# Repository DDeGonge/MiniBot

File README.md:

# MiniBot
Super cheap super tiny bots for....well I don't know yet

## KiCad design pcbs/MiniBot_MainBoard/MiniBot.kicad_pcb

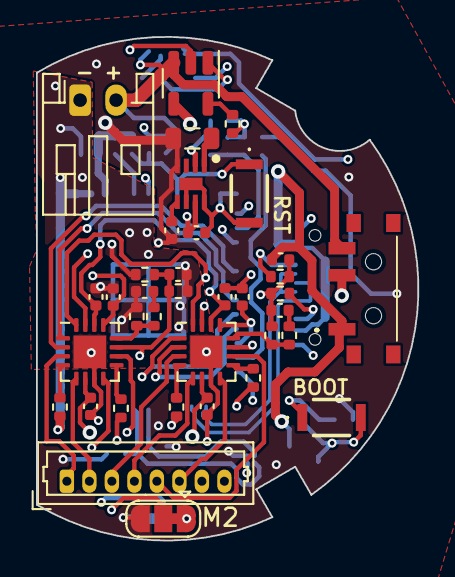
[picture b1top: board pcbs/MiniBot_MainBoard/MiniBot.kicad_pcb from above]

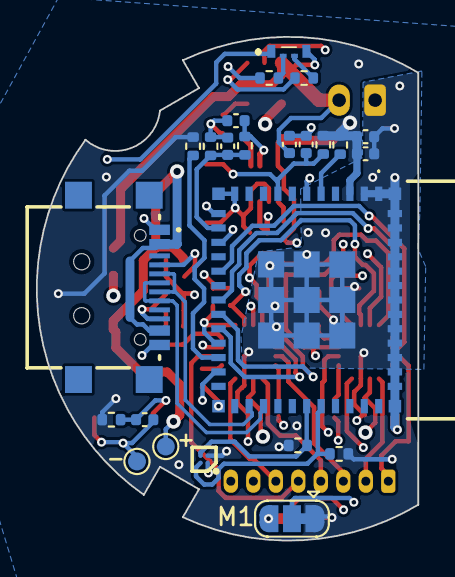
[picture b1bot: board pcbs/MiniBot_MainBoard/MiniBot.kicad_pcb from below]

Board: 4 copper layers, 21.2 x 28.0 mm, 60 parts (24 on the bottom side), 48 nets.

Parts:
C1, C8, C10: 4.7uF; C_0402_1005Metric
C2, C4, C5, C6, C9, C15, C16, C19, C20, C23: 0.1uF; C_0402_1005Metric
C3: 1uF; C_0402_1005Metric
C7: 560pF; C_0402_1005Metric
C17, C21: 10uF; C_0402_1005Metric
C18, C22: 22nF; C_0402_1005Metric
IC1: MMC5633NJL; BGA4C40P2X2_85X85X60
IC2: MIC23050-SYML-TR; SON50P200X200X90-9N-D
J1: Conn_01x08; Molex_PicoBlade_53047-0810_1x08_P1.25mm_Vertical
J2: Conn_01x02; JST_PH_S2B-PH-K_1x02_P2.00mm_Horizontal
J3: GSB1C41110SSHR
JP1, JP2: Jumper_3_Bridged12; SolderJumper-3_P1.3mm_Bridged12_RoundedPad1.0x1.5mm
L1: L; L_0805_2012Metric
LED1: EASV2010RWA0
R1, R2, R14, R15: 5.1k; R_0402_1005Metric
R3, R4, R5, R6, R9, R12: 10k; R_0402_1005Metric
R7, R10, R11: 390k; R_0402_1005Metric
R8: 12.4k; R_0402_1005Metric
R13, R16, R20: 1k; R_0402_1005Metric
R18, R19, R22, R23: 1; R_0402_1005Metric
R24, R25: 47k; R_0402_1005Metric
S1: PCM12SMTR
S2, S3: EVP-AWBD4A; EVPAWBD4A
TP1, TP2: TestPoint; TestPoint_Pad_D1.0mm
U1: ESP32-C3-MINI-1-H4X; ESP32C3MINI1H4X
U3: MCP73832-2-OT; SOT-23-5
U4, U5: STSPIN220; VQFN-16-1EP_3x3mm_P0.5mm_EP1.8x1.8mm

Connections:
+3V3: C1.2, C2.1, C7.1, IC1.B1 (VDD), IC2.4 (SNS), JP1.3 (B), JP2.1 (A), L1.1, R1.1, R2.1, R3.1, R5.1, R6.1, R7.1, R9.1, U1.3 (3V3)
+5V: C9.1, J3.A4 (VBUS_1), J3.A9 (VBUS_2), S1.1 (NC), TP2.1, U3.4 (V_{DD})
+BATT: C10.1, J2.2, LED1.4 (R6+), S1.3 (NO), U3.3 (V_{BAT})
/CC1: J3.A5 (CC1), R14.1
/CC2: J3.B5 (CC2), R15.1
/CFF: C7.2, IC2.5 (CFF)
/GPIO2: R6.2, U1.5 (IO2)
/GPIO8: R5.2, U1.22 (IO8)
/GPIO9: C5.1, R9.2, S3.A1 (NO), U1.23 (IO9)
/LED_R: LED1.3 (R6-), R13.1
/LED_W: LED1.1 (T1+), U1.12 (IO0)
/M0_A1: J1.1, U4.3 (OUTA1)
/M0_A2: J1.2, U4.5 (OUTA2)
/M0_B1: J1.8, U4.10 (OUTB1)
/M0_B2: J1.7, U4.8 (OUTB2)
/M0_DIR: U1.18 (IO4), U4.1 (DIR)
/M0_STEP: U1.16 (IO10), U4.2 (STCK)
/M1_A1: J1.3, U5.3 (OUTA1)
/M1_A2: J1.4, U5.5 (OUTA2)
/M1_B1: J1.5, U5.10 (OUTB1)
/M1_B2: J1.6, U5.8 (OUTB2)
/M1_DIR: U1.19 (IO5), U5.1 (DIR)
/M1_STEP: U1.20 (IO6), U5.2 (STCK)
/MODE1: JP2.2 (C), U4.16 (MODE1), U5.16 (MODE1)
/MODE2: JP1.2 (C), U4.15 (MODE2), U5.15 (MODE2)
/M_EN: C15.1, C19.1, U1.21 (IO7), U4.13 (EN/FLT), U5.13 (EN/FLT)
/M_RST: C16.1, C20.1, U1.6 (IO3), U4.14 (STBY/RESET), U5.14 (STBY/RESET)
/RST: C3.1, R3.2, S2.A1 (NO), U1.8 (EN)
/SCL: IC1.A2 (SCL), R1.2, U1.31 (TXD0)
/SDA: IC1.B2 (SDA), R2.2, U1.30 (RXD0)
/USB+: J3.A6 (DP1), J3.B6 (DP2), U1.27 (IO19)
/USB-: J3.A7 (DN1), J3.B7 (DN2), U1.26 (IO18)
/VREF: C4.1, R7.2, R8.1, U4.11 (REF), U5.11 (REF)
/VSENSE: C6.1, R10.2, R11.1, U1.13 (IO1)
GND: C1.1, C2.2, C3.2, C4.2, C5.2, C6.2, C8.2, C9.2, C10.2, C15.2, C16.2, C17.2, C18.2, C19.2, C20.2, C21.2, C22.2, C23.2, IC1.A1 (VSA), IC2.6 (AGND), IC2.8 (PGND), IC2.9 (EP), J2.1, J3.A1 (GND_1), J3.A12 (GND_2), JP1.1 (A), JP2.3 (B), R4.2, R8.2, R11.2, R12.2, R14.2, R15.2, R18.2, R19.2, R22.2, R23.2, R24.2, R25.2, S2.A2 (COM), S3.A2 (COM), TP1.1, U1.1 (GND_1), U1.2 (GND_2), U1.11 (GND_3), U1.14 (GND_4), U1.36 (GND_5), U1.37 (GND_6), U1.38 (GND_7), U1.39 (GND_8), U1.40 (GND_9), U1.41 (GND_10), U1.42 (GND_11), U1.43 (GND_12), U1.44 (GND_13), U1.45 (GND_14), U1.46 (GND_15), U1.47 (GND_16), U1.48 (GND_17), U1.49 (GND_18), U1.50 (GND_19), U1.51 (GND_20), U1.52 (GND_21), U1.53 (GND_22), U1.54 (GND_23), U1.55 (GND_24), U1.56 (GND_25), U1.57 (GND_26), U1.58 (GND_27), U1.59 (GND_28), U1.60 (GND_29), U1.61 (GND_30), U3.2 (V_{SS}), U4.7 (GND), U4.17 (EPAD), U5.7 (GND), U5.17 (EPAD)
unnamed: C18.1, R16.2
unnamed: C22.1, R20.2
unnamed: IC2.1 (SW), L1.2
unnamed: LED1.2 (T1-), R4.1
unnamed: R12.1, U3.5 (PROG)
unnamed: R13.2, U3.1 (STAT)
unnamed: R19.1, U4.4 (SENSEA)
unnamed: R18.1, U4.9 (SENSEB)
unnamed: R16.1, R24.1, U4.12 (TOFF)
unnamed: R23.1, U5.4 (SENSEA)
unnamed: R22.1, U5.9 (SENSEB)
unnamed: R20.1, R25.1, U5.12 (TOFF)
VDC: C8.1, C17.1, C21.1, C23.1, IC2.2 (EN), IC2.7 (VIN), R10.1, S1.2 (COM), U4.6 (VS), U5.6 (VS)

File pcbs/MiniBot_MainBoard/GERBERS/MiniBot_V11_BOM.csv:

Item #,*Designator,*Qty,Manufacturer,*Mfg Part #,Description / Value,*Package/Footprint,Type,Your Instructions / Notes
1,U1,1,Espressif Systems,ESP32-C3-MINI-1-H4X,ESP32-C3-MINI-1-H4X,ESP32C3MINI1H4X,SMD,
2,U3,1,Microchip Technology,MCP73832-2-OT,IC BATT CONTRL LI-ION 1CELL 8DFN,8-VFDFN,SMD,
3,"U4,U5",2,STMicroelectronics,STSPIN220,LOW VOLTAGE STEPPER MOTOR DRIVER,VQFN-16,SMD,
4,IC1,1,Memsic Inc.,MMC5633NJL,SEN MR I2C/I3C 4-WLP,4-WLP,BGA,
5,IC2,1,Microchip Technology,MIC23050-SYML-TR,High Efficiency 600mA Buck Switcher,8-VFDFN,SMD,
6,S1,1,C&K,PCM12SMTR,SWITCH SLIDE SPDT 300MA 6V,SMD,SMD,
7,"S2,S3",2,Panasonic,EVP-AWBD4A,Tactile Switches EVP-AWBD4A,SMD,SMD,
8,L1,1,TKD,MLZ2012N1R0LT000,Power Inductors - SMD 1 UH 20%,805,SMD,
9,LED1,1,Everlight Electronics Co Ltd,EASV2010RWA0,LED RED/WHITE DIFFUSED 4SMD R/A,SMD,SMD,
10,"R22,R19,R23,R18",4,YAGEO,RC0402FR-7W1RL,RES 1 OHM 1% 1/8W 0402,402,SMD,Substitutions OK
11,"R20,R16,R13",3,YAGEO,RC0402FR-071KL,RES 1K OHM 1% 1/16W 0402,402,SMD,Substitutions OK
12,"R15,R14,R1,R2",4,YAGEO,RC0402FR-135K1L,RES 5.1K OHM 1% 1/16W 0402,402,SMD,Substitutions OK
13,"R12,R9,R3,R5,R4,R6",6,YAGEO,RC0402FR-0710KL,RES 10K OHM 1% 1/16W 0402,402,SMD,Substitutions OK
14,R8,1,YAGEO,RC0402FR-0712K4L,RES 12.4K OHM 1% 1/16W 0402,402,SMD,Substitutions OK
15,"R24,R25",2,YAGEO,RC0402FR-0747KL,RES 47K OHM 1% 1/16W 0402,402,SMD,Substitutions OK
16,"R7,R10,R11",3,YAGEO,RC0402FR-07390KL,RES 390K OHM 1% 1/16W 0402,402,SMD,Substitutions OK
17,C7,1,Murata Electronics,GRM1555C1H561JA01D,CAP CER 560PF 50V C0G/NP0 0402,402,SMD,Substitutions OK
18,"C22,C18",2,Murata Electronics,GRM155R71C223KA01D,CAP CER 0.022UF 16V X7R 0402,402,SMD,Substitutions OK
19,"C16,C9,C19,C15,C20,C23,C4,C5,C6,C2",10,Murata Electronics,GRM155R71C104KA88J,CAP CER 0.1 uF 16 VDC 10% 0402 X7R,402,SMD,Substitutions OK
20,C3,1,Murata Electronics,GCM155C71A105KE38D,CAP CER 1UF 10V X7S 0402,402,SMD,Substitutions OK
21,"C1,C10,C8",3,Murata Electronics,GRM155R60J475ME47D,CAP CER 4.7UF 6.3V X5R 0402,402,SMD,Substitutions OK
22,"C21,C17",2,Murata Electronics,GRM155R60J106ME05J,CAP CER 10UF 6.3V X5R 0402,402,SMD,Substitutions OK
23,J1,1,Molex,530470810,CONN HEADER VERT 8POS 1.25MM,1x08_P1.25mm,Through Hole,
24,J2,1,JST,S2B-PH-K-S,CONN HEADER R/A 2POS 2MM,1x02_P2.00mm,Through Hole,
25,J3,1,Amphenol Canada,GSB1C41110SSHR,USB Connectors USB2.0 TYPE C,SMD,SMD,

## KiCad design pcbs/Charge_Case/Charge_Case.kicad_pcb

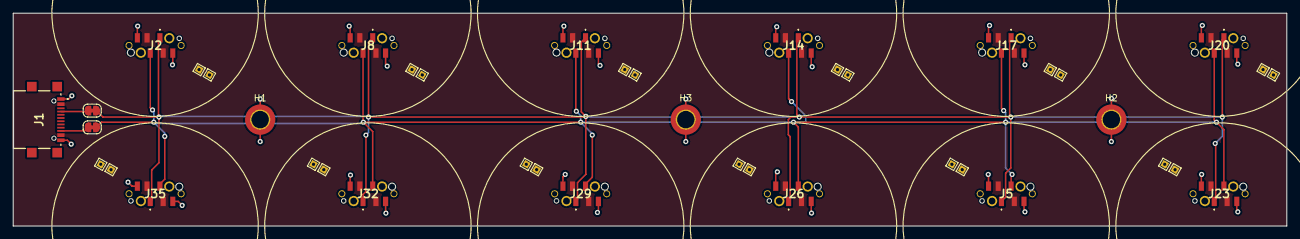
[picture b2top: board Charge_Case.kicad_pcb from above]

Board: 2 copper layers, 197.5 x 33.0 mm, 42 parts (0 on the bottom side), 8 nets.

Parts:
H1, H2, H3: MountingHole_Pad; MountingHole_2.7mm_M2.5_DIN965_Pad_TopOnly
J1: GSB1C41110SSHR
J2, J5, J8, J11, J14, J17, J20, J23, J26, J29, J32, J35: USB4180-03-0120-C; USB4180030120C
J3, J4, J6, J7, J9, J10, J12, J13, J15, J16, J18, J19, J21, J22, J24, J25, J27, J28, J30, J31, J33, J34, J36, J37: Conn_01x01; TestPoint_THTPad_1.0x1.0mm_Drill0.5mm
JP1, JP2: Jumper_2_Bridged; SolderJumper-2_P1.3mm_Bridged_RoundedPad1.0x1.5mm

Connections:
+5V: J1.A4 (VBUS_1), J1.A9 (VBUS_2), J2.A9 (VBUS_1), J2.B9 (VBUS_2), J3.1, J5.A9 (VBUS_1), J5.B9 (VBUS_2), J6.1, J8.A9 (VBUS_1), J8.B9 (VBUS_2), J9.1, J11.A9 (VBUS_1), J11.B9 (VBUS_2), J12.1, J14.A9 (VBUS_1), J14.B9 (VBUS_2), J15.1, J17.A9 (VBUS_1), J17.B9 (VBUS_2), J18.1, J20.A9 (VBUS_1), J20.B9 (VBUS_2), J21.1, J23.A9 (VBUS_1), J23.B9 (VBUS_2), J24.1, J26.A9 (VBUS_1), J26.B9 (VBUS_2), J27.1, J29.A9 (VBUS_1), J29.B9 (VBUS_2), J30.1, J32.A9 (VBUS_1), J32.B9 (VBUS_2), J33.1, J35.A9 (VBUS_1), J35.B9 (VBUS_2), J36.1
/CC1: J2.A5 (CC1), J5.A5 (CC1), J8.A5 (CC1), J11.A5 (CC1), J14.A5 (CC1), J17.A5 (CC1), J20.A5 (CC1), J23.A5 (CC1), J26.A5 (CC1), J29.A5 (CC1), J32.A5 (CC1), J35.A5 (CC1), JP1.1 (A)
/CC1_SRC: J1.A5 (CC1), JP1.2 (B)
/CC2: J2.B5 (CC2), J5.B5 (CC2), J8.B5 (CC2), J11.B5 (CC2), J14.B5 (CC2), J17.B5 (CC2), J20.B5 (CC2), J23.B5 (CC2), J26.B5 (CC2), J29.B5 (CC2), J32.B5 (CC2), J35.B5 (CC2), JP2.1 (A)
/CC2_SRC: J1.B5 (CC2), JP2.2 (B)
GND: H1.1, H2.1, H3.1, J1.A1 (GND_1), J1.A12 (GND_2), J2.A12 (GND_1), J2.B12 (GND_2), J4.1, J5.A12 (GND_1), J5.B12 (GND_2), J7.1, J8.A12 (GND_1), J8.B12 (GND_2), J10.1, J11.A12 (GND_1), J11.B12 (GND_2), J13.1, J14.A12 (GND_1), J14.B12 (GND_2), J16.1, J17.A12 (GND_1), J17.B12 (GND_2), J19.1, J20.A12 (GND_1), J20.B12 (GND_2), J22.1, J23.A12 (GND_1), J23.B12 (GND_2), J25.1, J26.A12 (GND_1), J26.B12 (GND_2), J28.1, J29.A12 (GND_1), J29.B12 (GND_2), J31.1, J32.A12 (GND_1), J32.B12 (GND_2), J34.1, J35.A12 (GND_1), J35.B12 (GND_2), J37.1
unnamed: J1.A6 (DP1), J1.A7 (DN1)
unnamed: J1.B6 (DP2), J1.B7 (DN2)

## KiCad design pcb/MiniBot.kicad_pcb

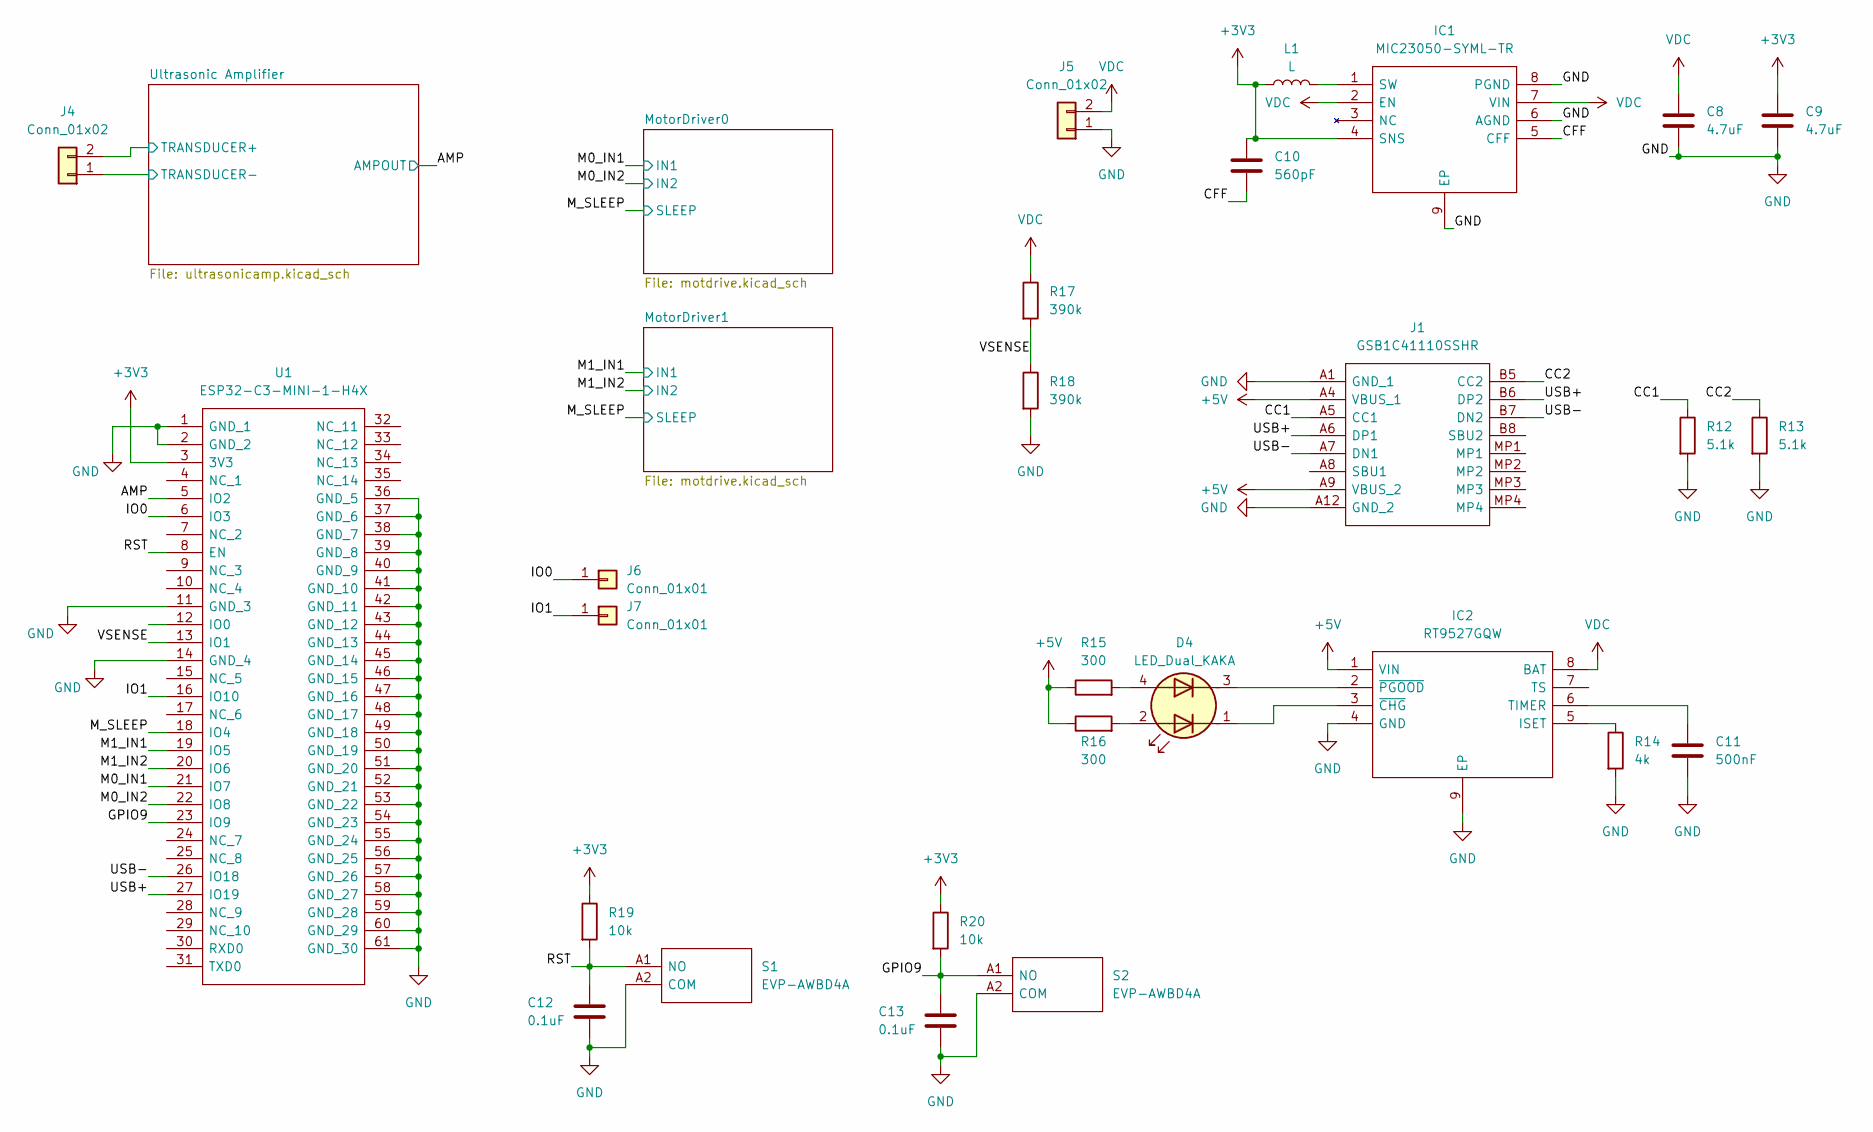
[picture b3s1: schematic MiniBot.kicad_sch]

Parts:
C8, C9: 4.7uF; C_0402_1005Metric
C10: 560pF; C_0402_1005Metric
C11: 500nF; C_0402_1005Metric
C12, C13: 0.1uF; C_0402_1005Metric
D4: LED_Dual_KAKA; SB0603WC01-RG
IC1: MIC23050-SYML-TR; SON50P200X200X90-9N-D; Mouser Part Number 998-MIC23050-SYMLTR
IC2: RT9527GQW; SON50P200X200X80-9N; Mouser Part Number 835-RT9527GQW
J1: GSB1C41110SSHR; Manufacturer_Part_Number GSB1C41110SSHR
J4: Conn_01x02; Transducer
J5: Conn_01x02; JST_PH_S2B-PH-K_1x02_P2.00mm_Horizontal
J6, J7: Conn_01x01; TestPoint_Pad_D1.0mm
L1: L; L_0805_2012Metric
R12, R13: 5.1k; R_0402_1005Metric
R14: 4k; R_0402_1005Metric
R15, R16: 300; R_0402_1005Metric
R17, R18: 390k; R_0402_1005Metric
R19, R20: 10k; R_0402_1005Metric
S1, S2: EVP-AWBD4A; EVPAWBD4A; Mouser Part Number 667-EVP-AWBD4A
U1: ESP32-C3-MINI-1-H4X; ESP32C3MINI1H4X; Mouser Part Number 356-ESP32C3MINI1H4X

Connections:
+3V3: C9.1, C10.1, IC1.4 (SNS), L1.1, R19.1, R20.1, U1.3 (3V3); also elsewhere on the board
+5V: IC2.1 (VIN), J1.A4 (VBUS_1), J1.A9 (VBUS_2), R15.1, R16.1
/AMP: U1.5 (IO2); also elsewhere on the board
/CC1: J1.A5 (CC1), R12.1
/CC2: J1.B5 (CC2), R13.1
/CFF: C10.2, IC1.5 (CFF)
/GPIO9: C13.1, R20.2, S2.A1 (NO), U1.23 (IO9)
/IO0: J6.1, U1.6 (IO3)
/IO1: J7.1, U1.16 (IO10)
/M0_IN1: U1.21 (IO7); also elsewhere on the board
/M0_IN2: U1.22 (IO8); also elsewhere on the board
/M1_IN1: U1.19 (IO5); also elsewhere on the board
/M1_IN2: U1.20 (IO6); also elsewhere on the board
/M_SLEEP: U1.18 (IO4); also elsewhere on the board
/RST: C12.1, R19.2, S1.A1 (NO), U1.8 (EN)
/USB+: J1.A6 (DP1), J1.B6 (DP2), U1.27 (IO19)
/USB-: J1.A7 (DN1), J1.B7 (DN2), U1.26 (IO18)
/Ultrasonic Amplifier/IN1+: J4.2; also elsewhere on the board
/VSENSE: R17.2, R18.1, U1.13 (IO1)
GND: C8.2, C9.2, C11.2, C12.2, C13.2, IC1.6 (AGND), IC1.8 (PGND), IC1.9 (EP), IC2.4 (GND), IC2.9 (EP), J1.A1 (GND_1), J1.A12 (GND_2), J4.1, J5.1, R12.2, R13.2, R14.2, R18.2, S1.A2 (COM), S2.A2 (COM), U1.1 (GND_1), U1.2 (GND_2), U1.11 (GND_3), U1.14 (GND_4), U1.36 (GND_5), U1.37 (GND_6), U1.38 (GND_7), U1.39 (GND_8), U1.40 (GND_9), U1.41 (GND_10), U1.42 (GND_11), U1.43 (GND_12), U1.44 (GND_13), U1.45 (GND_14), U1.46 (GND_15), U1.47 (GND_16), U1.48 (GND_17), U1.49 (GND_18), U1.50 (GND_19), U1.51 (GND_20), U1.52 (GND_21), U1.53 (GND_22), U1.54 (GND_23), U1.55 (GND_24), U1.56 (GND_25), U1.57 (GND_26), U1.58 (GND_27), U1.59 (GND_28), U1.60 (GND_29), U1.61 (GND_30); also elsewhere on the board
unnamed: D4.1 (A1), IC2.3 (~CHG)
unnamed: D4.3 (A2), IC2.2 (~PGOOD)
unnamed: D4.2 (K1), R16.2
unnamed: D4.4 (K2), R15.2
unnamed: IC1.1 (SW), L1.2
unnamed: IC2.5 (ISET), R14.1
unnamed: C11.1, IC2.6 (TIMER)
VDC: C8.1, IC1.2 (EN), IC1.7 (VIN), IC2.8 (BAT), J5.2, R17.1; also elsewhere on the board

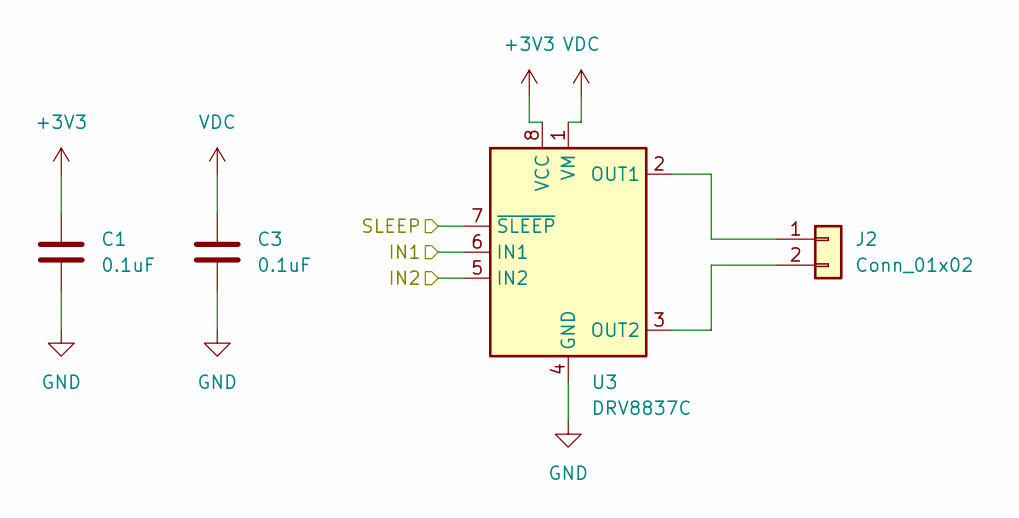
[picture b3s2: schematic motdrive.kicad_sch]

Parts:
C1, C3: 0.1uF; C_0402_1005Metric
J2: Conn_01x02; PinHeader_1x02_P1.27mm_Vertical
U3: DRV8837C; WSON-8-1EP_2x2mm_P0.5mm_EP0.9x1.6mm

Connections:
+3V3: C1.1, U3.8 (VCC); also elsewhere on the board
/M0_IN1: U3.6 (IN1); also elsewhere on the board
/M0_IN2: U3.5 (IN2); also elsewhere on the board
/M_SLEEP: U3.7 (~SLEEP); also elsewhere on the board
GND: C1.2, C3.2, U3.4 (GND), U3.9 (GND); also elsewhere on the board
unnamed: J2.1, U3.2 (OUT1)
unnamed: J2.2, U3.3 (OUT2)
VDC: C3.1, U3.1 (VM); also elsewhere on the board

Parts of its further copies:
C2, C4: 0.1uF; C_0402_1005Metric
J3: Conn_01x02; PinHeader_1x02_P1.27mm_Vertical
U4: DRV8837C; WSON-8-1EP_2x2mm_P0.5mm_EP0.9x1.6mm

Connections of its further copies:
+3V3: C2.1, U4.8 (VCC); also elsewhere on the board
/M1_IN1: U4.6 (IN1); also elsewhere on the board
/M1_IN2: U4.5 (IN2); also elsewhere on the board
/M_SLEEP: U4.7 (~SLEEP); also elsewhere on the board
GND: C2.2, C4.2, U4.4 (GND), U4.9 (GND); also elsewhere on the board
unnamed: J3.1, U4.2 (OUT1)
unnamed: J3.2, U4.3 (OUT2)
VDC: C4.1, U4.1 (VM); also elsewhere on the board

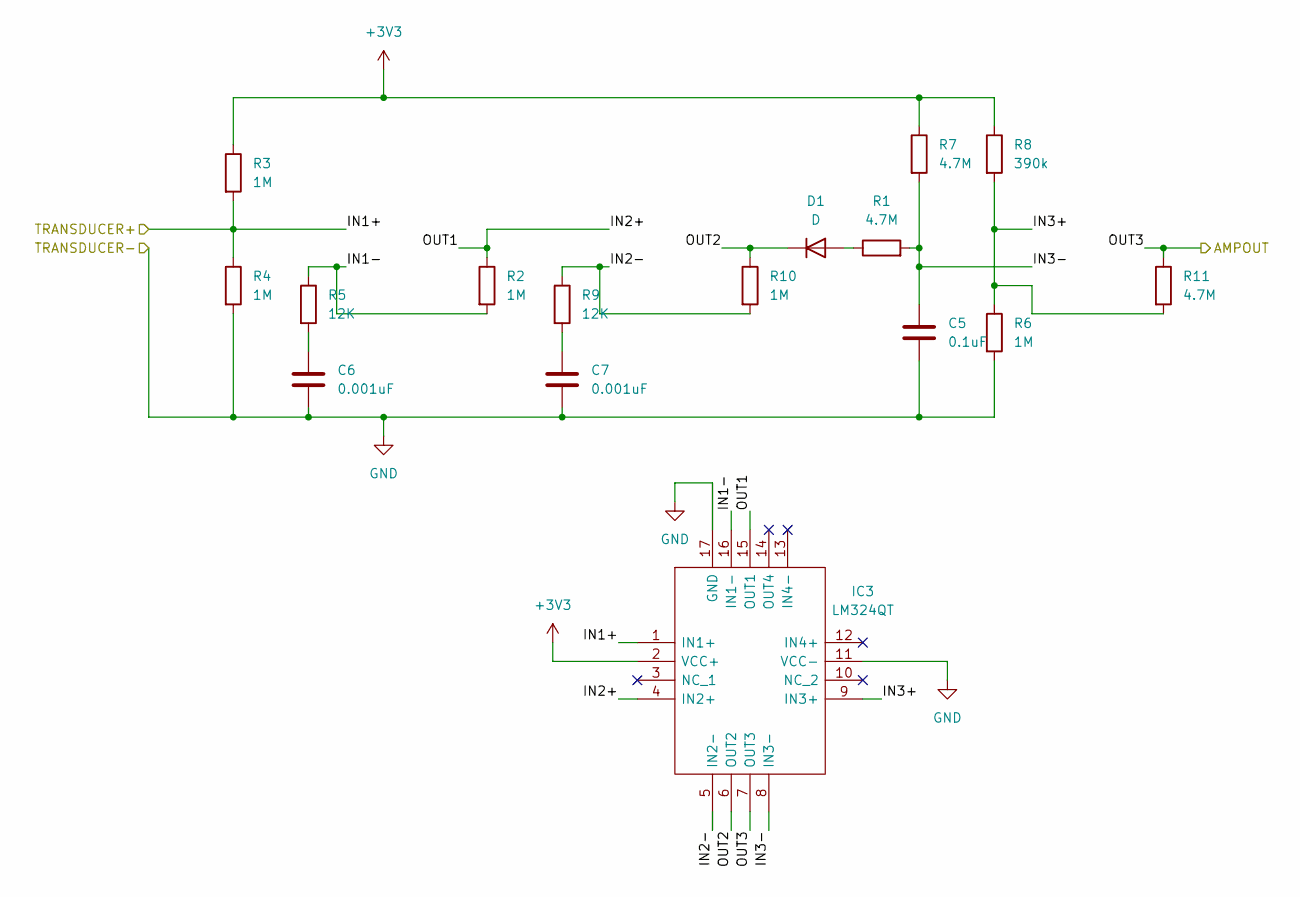
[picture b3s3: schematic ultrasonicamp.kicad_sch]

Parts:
C5: 0.1uF; C_0402_1005Metric
C6, C7: 0.001uF; C_0402_1005Metric
D1: D; D_0402_1005Metric
IC3: LM324QT; QFN50P300X300X100-17N; Mouser Part Number 511-LM324QT
R1, R7, R11: 4.7M; R_0402_1005Metric
R2, R3, R4, R6, R10: 1M; R_0402_1005Metric
R5, R9: 12K; R_0402_1005Metric
R8: 390k; R_0402_1005Metric

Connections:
+3V3: IC3.2 (VCC+), R3.1, R7.1, R8.1; also elsewhere on the board
/AMP: IC3.7 (OUT3), R11.1; also elsewhere on the board
/Ultrasonic Amplifier/IN1+: IC3.1 (IN1+), R3.2, R4.1; also elsewhere on the board
/Ultrasonic Amplifier/IN1-: IC3.16 (IN1-), R2.2, R5.1
/Ultrasonic Amplifier/IN2+: IC3.4 (IN2+), IC3.15 (OUT1), R2.1
/Ultrasonic Amplifier/IN2-: IC3.5 (IN2-), R9.1, R10.2
/Ultrasonic Amplifier/IN3+: IC3.9 (IN3+), R6.1, R8.2, R11.2
/Ultrasonic Amplifier/IN3-: C5.1, IC3.8 (IN3-), R1.2, R7.2
/Ultrasonic Amplifier/OUT2: D1.1 (K), IC3.6 (OUT2), R10.1
GND: C5.2, C6.2, C7.2, IC3.11 (VCC-), IC3.17 (GND), R4.2, R6.2; also elsewhere on the board
unnamed: C6.1, R5.2
unnamed: C7.1, R9.2
unnamed: D1.2 (A), R1.1

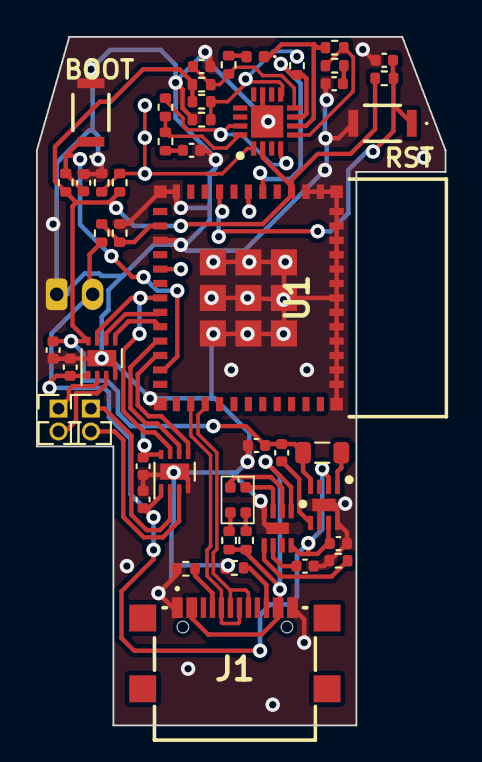
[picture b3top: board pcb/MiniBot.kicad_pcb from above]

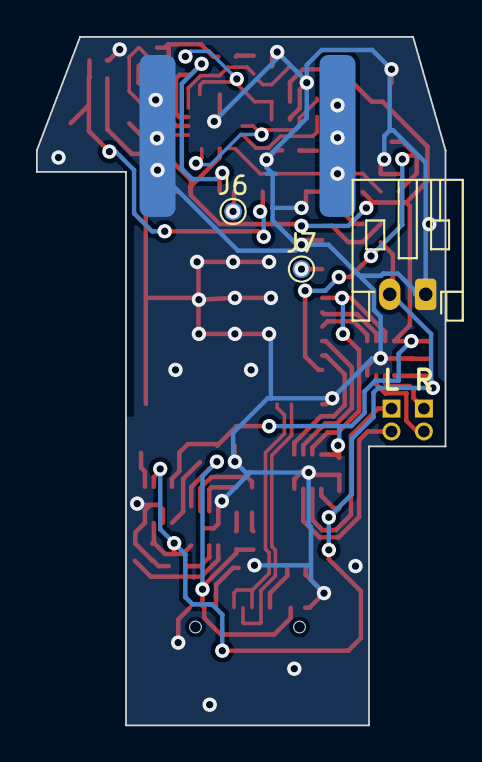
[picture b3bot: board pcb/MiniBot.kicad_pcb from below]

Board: 2 copper layers, 22.7 x 38.2 mm, 51 parts (4 on the bottom side), 41 nets.

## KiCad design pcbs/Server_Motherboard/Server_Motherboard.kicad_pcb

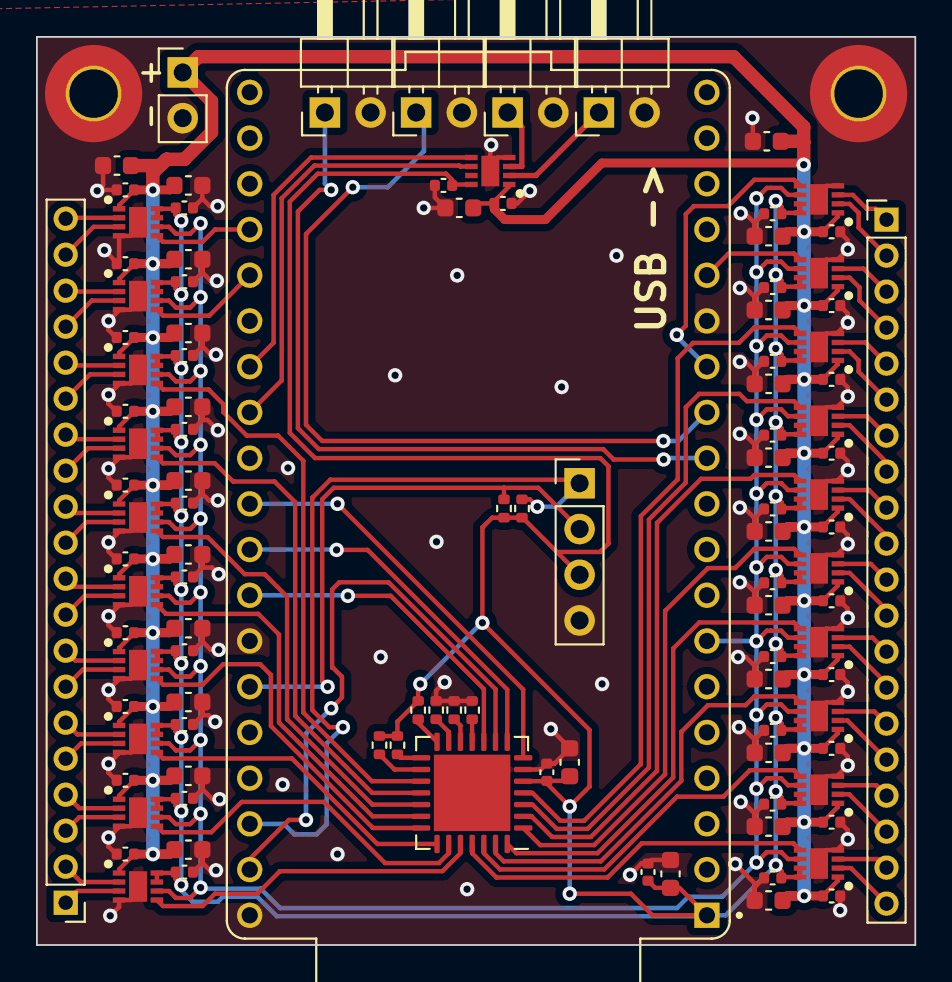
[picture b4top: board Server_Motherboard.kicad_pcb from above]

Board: 2 copper layers, 48.8 x 50.4 mm, 110 parts (0 on the bottom side), 82 nets.

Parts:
C1, C3, C5, C7, C9, C11, C13, C15, C17, C19, C21, C23, C25, C27, C29, C31, C33, C35, C37, C39, C41, C64, C65, C66, C68: 10uF; C_0603_1608Metric
C2, C4, C6, C8, C10, C12, C14, C16, C18, C20, C22, C24, C26, C28, C30, C32, C34, C36, C38, C40, C42, C43, C44, C45, C46, C47, C48, C49, C50, C51, C52, C53, C54, C55, C56, C57, C58, C59, C60, C61, C62, C63, C67, C69: 0.1uF; C_0402_1005Metric
H1, H2: MountingHole_Pad; MountingHole_2.7mm_M2.5_Pad_TopBottom
IC1, IC21, IC22, IC23, IC24, IC25, IC26, IC27, IC28, IC29, IC30, IC31, IC32, IC33, IC34, IC35, IC36, IC37, IC38, IC39, IC40: DRV8210DSGR; SON50P200X200X80-9N
J1, J2: Conn_01x20; PinHeader_1x20_P2.00mm_Vertical
J3: Conn_01x02; PinHeader_1x02_P2.54mm_Vertical
J4: Conn_01x04; PinHeader_1x04_P2.54mm_Vertical
J5, J6, J7, J8: Conn_01x02; PinHeader_1x02_P2.54mm_Horizontal
R1, R2, R3, R4, R5, R6, R7, R8: 10k; R_0402_1005Metric
U1: ESP32-DEVKITC-32E; MODULE_ESP32-DEVKITC-32E
U2: MCP23S17_ML; QFN-28-1EP_6x6mm_P0.65mm_EP4.25x4.25mm

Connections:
+3V3: C2.1, C43.1, C44.1, C45.1, C46.1, C47.1, C48.1, C49.1, C50.1, C51.1, C52.1, C53.1, C54.1, C55.1, C56.1, C57.1, C58.1, C59.1, C60.1, C61.1, C62.1, C63.1, C64.1, C65.1, C67.1, IC1.8 (VCC), IC21.7 (MODE), IC21.8 (VCC), IC22.7 (MODE), IC22.8 (VCC), IC23.7 (MODE), IC23.8 (VCC), IC24.7 (MODE), IC24.8 (VCC), IC25.7 (MODE), IC25.8 (VCC), IC26.7 (MODE), IC26.8 (VCC), IC27.7 (MODE), IC27.8 (VCC), IC28.7 (MODE), IC28.8 (VCC), IC29.7 (MODE), IC29.8 (VCC), IC30.7 (MODE), IC30.8 (VCC), IC31.7 (MODE), IC31.8 (VCC), IC32.7 (MODE), IC32.8 (VCC), IC33.7 (MODE), IC33.8 (VCC), IC34.7 (MODE), IC34.8 (VCC), IC35.7 (MODE), IC35.8 (VCC), IC36.7 (MODE), IC36.8 (VCC), IC37.7 (MODE), IC37.8 (VCC), IC38.7 (MODE), IC38.8 (VCC), IC39.7 (MODE), IC39.8 (VCC), IC40.7 (MODE), IC40.8 (VCC), J4.3, R1.1, R2.1, R6.1, R7.1, R8.1, U1.J2_1 (3V3), U2.5 (VDD)
/A0: R3.1, U2.11 (A0)
/A1: R4.1, U2.12 (A1)
/A2: R5.1, U2.13 (A2)
/COIL0_A: IC21.2 (OUT1), J1.20
/COIL0_B: IC21.3 (OUT2), J1.19
/COIL1_A: IC22.2 (OUT1), J1.18
/COIL1_B: IC22.3 (OUT2), J1.17
/COIL2_A: IC23.2 (OUT1), J1.16
/COIL2_B: IC23.3 (OUT2), J1.15
/COIL3_A: IC24.2 (OUT1), J1.14
/COIL3_B: IC24.3 (OUT2), J1.13
/COIL4_A: IC25.2 (OUT1), J1.12
/COIL4_B: IC25.3 (OUT2), J1.11
/COIL5_A: IC26.2 (OUT1), J1.10
/COIL5_B: IC26.3 (OUT2), J1.9
/COIL6_A: IC27.2 (OUT1), J1.8
/COIL6_B: IC27.3 (OUT2), J1.7
/COIL7_A: IC28.2 (OUT1), J1.6
/COIL7_B: IC28.3 (OUT2), J1.5
/COIL8_A: IC29.2 (OUT1), J1.4
/COIL8_B: IC29.3 (OUT2), J1.3
/COIL9_A: IC30.2 (OUT1), J1.2
/COIL9_B: IC30.3 (OUT2), J1.1
/COIL10_A: IC31.2 (OUT1), J2.20
/COIL10_B: IC31.3 (OUT2), J2.19
/COIL11_A: IC32.2 (OUT1), J2.18
/COIL11_B: IC32.3 (OUT2), J2.17
/COIL12_A: IC33.2 (OUT1), J2.16
/COIL12_B: IC33.3 (OUT2), J2.15
/COIL13_A: IC34.2 (OUT1), J2.14
/COIL13_B: IC34.3 (OUT2), J2.13
/COIL14_A: IC35.2 (OUT1), J2.12
/COIL14_B: IC35.3 (OUT2), J2.11
/COIL15_A: IC36.2 (OUT1), J2.10
/COIL15_B: IC36.3 (OUT2), J2.9
/COIL16_A: IC37.2 (OUT1), J2.8
/COIL16_B: IC37.3 (OUT2), J2.7
/COIL17_A: IC38.2 (OUT1), J2.6
/COIL17_B: IC38.3 (OUT2), J2.5
/COIL18_A: IC39.2 (OUT1), J2.4
/COIL18_B: IC39.3 (OUT2), J2.3
/COIL19_A: IC40.2 (OUT1), J2.2
/COIL19_B: IC40.3 (OUT2), J2.1
/COIL_DIR: IC21.6 (IN1/PH), IC22.6 (IN1/PH), IC23.6 (IN1/PH), IC24.6 (IN1/PH), IC25.6 (IN1/PH), IC26.6 (IN1/PH), IC27.6 (IN1/PH), IC28.6 (IN1/PH), IC29.6 (IN1/PH), IC30.6 (IN1/PH), IC31.6 (IN1/PH), IC32.6 (IN1/PH), IC33.6 (IN1/PH), IC34.6 (IN1/PH), IC35.6 (IN1/PH), IC36.6 (IN1/PH), IC37.6 (IN1/PH), IC38.6 (IN1/PH), IC39.6 (IN1/PH), IC40.6 (IN1/PH), U1.J2_7 (IO32)
/C_EN_0: IC21.5 (IN2/EN), U1.J3_16 (IO15)
/C_EN_1: IC22.5 (IN2/EN), U1.J3_15 (IO2)
/C_EN_2: IC23.5 (IN2/EN), U2.17 (GPA0)
/C_EN_3: IC24.5 (IN2/EN), U2.18 (GPA1)
/C_EN_4: IC25.5 (IN2/EN), U2.19 (GPA2)
/C_EN_5: IC26.5 (IN2/EN), U2.20 (GPA3)
/C_EN_6: IC27.5 (IN2/EN), U2.21 (GPA4)
/C_EN_7: IC28.5 (IN2/EN), U2.22 (GPA5)
/C_EN_8: IC29.5 (IN2/EN), U2.23 (GPA6)
/C_EN_9: IC30.5 (IN2/EN), U2.24 (GPA7)
/C_EN_10: IC31.5 (IN2/EN), U2.25 (GPB0)
/C_EN_11: IC32.5 (IN2/EN), U2.26 (GPB1)
/C_EN_12: IC33.5 (IN2/EN), U2.27 (GPB2)
/C_EN_13: IC34.5 (IN2/EN), U2.28 (GPB3)
/C_EN_14: IC35.5 (IN2/EN), U2.1 (GPB4)
/C_EN_15: IC36.5 (IN2/EN), U2.2 (GPB5)
/C_EN_16: IC37.5 (IN2/EN), U2.3 (GPB6)
/C_EN_17: IC38.5 (IN2/EN), U2.4 (GPB7)
/C_EN_18: IC39.5 (IN2/EN), U1.J2_15 (IO13)
/C_EN_19: IC40.5 (IN2/EN), U1.J2_13 (IO12)
/GPIO_CS: U1.J3_10 (IO5), U2.7 (~CS)
/INTA: R7.2, U2.16 (INTA)
/INTB: R8.2, U2.15 (INTB)
/MISO: U1.J3_8 (IO19), U2.10 (SO)
/MOSI: U1.J3_2 (IO23), U2.9 (SI)
/RESET: R6.2, U2.14 (~RESET)
/SCK: U1.J3_9 (IO18), U2.8 (SCK)
/SCL: J4.1, R1.2, U1.J3_3 (IO22)
/SDA: J4.2, R2.2, U1.J3_6 (IO21)
/SOL_0: IC1.3 (OUT2), J5.1
/SOL_1: IC1.2 (OUT1), J6.1
/SOL_EN_0: IC1.6 (IN1/PH), U1.J3_12 (IO16)
/SOL_EN_1: IC1.5 (IN2/EN), U1.J3_13 (IO4)
/SW1: J7.1, U1.J2_11 (IO27)
/SW2: J8.1, U1.J2_12 (IO14)
GND: C1.1, C2.2, C3.2, C4.2, C5.2, C6.2, C7.2, C8.2, C9.2, C10.2, C11.2, C12.2, C13.2, C14.2, C15.2, C16.2, C17.2, C18.2, C19.2, C20.2, C21.2, C22.2, C23.2, C24.2, C25.2, C26.2, C27.2, C28.2, C29.2, C30.2, C31.2, C32.2, C33.2, C34.2, C35.2, C36.2, C37.2, C38.2, C39.2, C40.2, C41.2, C42.2, C43.2, C44.2, C45.2, C46.2, C47.2, C48.2, C49.2, C50.2, C51.2, C52.2, C53.2, C54.2, C55.2, C56.2, C57.2, C58.2, C59.2, C60.2, C61.2, C62.2, C63.2, C64.2, C65.2, C66.2, C67.2, C68.2, C69.2, H1.1, H2.1, IC1.4 (GND), IC1.9 (EP), IC21.4 (GND), IC21.9 (EP), IC22.4 (GND), IC22.9 (EP), IC23.4 (GND), IC23.9 (EP), IC24.4 (GND), IC24.9 (EP), IC25.4 (GND), IC25.9 (EP), IC26.4 (GND), IC26.9 (EP), IC27.4 (GND), IC27.9 (EP), IC28.4 (GND), IC28.9 (EP), IC29.4 (GND), IC29.9 (EP), IC30.4 (GND), IC30.9 (EP), IC31.4 (GND), IC31.9 (EP), IC32.4 (GND), IC32.9 (EP), IC33.4 (GND), IC33.9 (EP), IC34.4 (GND), IC34.9 (EP), IC35.4 (GND), IC35.9 (EP), IC36.4 (GND), IC36.9 (EP), IC37.4 (GND), IC37.9 (EP), IC38.4 (GND), IC38.9 (EP), IC39.4 (GND), IC39.9 (EP), IC40.4 (GND), IC40.9 (EP), J3.2, J4.4, J5.2, J6.2, J7.2, J8.2, R3.2, R4.2, R5.2, U1.J2_14 (GND_J2_14), U1.J3_1 (GND_J3_1), U1.J3_7 (GND_J3_7), U2.6 (VSS), U2.29 (EP)
VDC: C1.2, C3.1, C4.1, C5.1, C6.1, C7.1, C8.1, C9.1, C10.1, C11.1, C12.1, C13.1, C14.1, C15.1, C16.1, C17.1, C18.1, C19.1, C20.1, C21.1, C22.1, C23.1, C24.1, C25.1, C26.1, C27.1, C28.1, C29.1, C30.1, C31.1, C32.1, C33.1, C34.1, C35.1, C36.1, C37.1, C38.1, C39.1, C40.1, C41.1, C42.1, C66.1, C68.1, C69.1, IC1.1 (VM), IC21.1 (VM), IC22.1 (VM), IC23.1 (VM), IC24.1 (VM), IC25.1 (VM), IC26.1 (VM), IC27.1 (VM), IC28.1 (VM), IC29.1 (VM), IC30.1 (VM), IC31.1 (VM), IC32.1 (VM), IC33.1 (VM), IC34.1 (VM), IC35.1 (VM), IC36.1 (VM), IC37.1 (VM), IC38.1 (VM), IC39.1 (VM), IC40.1 (VM), J3.1

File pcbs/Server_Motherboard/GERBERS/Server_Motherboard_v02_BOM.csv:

Item #,*Designator,*Qty,Manufacturer,*Mfg Part #,Description / Value,*Package/Footprint,Type,Your Instructions / Notes
1,U2,1,Microchip Technology,MCP23S17-E/ML,IC XPNDR 10MHZ SPI 28QFN,SMD,SMD,
2,"IC32,IC33,IC29,IC23,IC39,IC36,IC28,IC34,IC27,IC31,IC30,IC24,IC1,IC35,IC40,IC26,IC38,IC21,IC25,IC22,IC37",21,Texas Instruments,DRV8210DSGR,"11V, 1A BRUSHED DC MOTOR DRIVER",SMD,SMD,
3,"R7,R5,R8,R6,R1,R4,R3,R2",8,YAGEO,RC0402FR-0710KL,RES 10K OHM 1% 1/16W 0402,0402,SMD,Substitutions OK
4,"C67,C12,C54,C24,C61,C45,C51,C59,C26,C40,C47,C52,C63,C34,C50,C4,C60,C10,C32,C43,C18,C14,C28,C8,C62,C42,C2,C49,C36,C16,C58,C57,C6,C38,C22,C46,C30,C56,C20,C69,C53,C55,C44,C48",44,Murata Electronics,GRM155R71C104KA88J,CAP CER 0.1 uF 16 VDC 10% 0402 X7R,0402,SMD,Substitutions OK
5,"C5,C66,C65,C35,C37,C25,C19,C39,C31,C7,C11,C68,C15,C29,C17,C33,C9,C3,C13,C41,C21,C27,C64,C1,C23",25,Murata Electronics,GRM188R6YA106MA73D,CAP CER 10UF 35V X5R 0603,0603,SMD,Substitutions OK

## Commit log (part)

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2025-02-13 initial pcb order
2026-05-01 speed and qol changes
2026-05-04 joystick fixes
2026-05-08 garbage fixing
2026-05-11 update coordinator with looper function from main branch
2026-06-22 update gitignore
2026-06-22 reformat and added autoformat scripts
2026-06-22 remove file
2026-06-22 c files reformat
2026-06-22 Update roadmap
    Added section on power optimizations for battery life improvements, plus some other details
